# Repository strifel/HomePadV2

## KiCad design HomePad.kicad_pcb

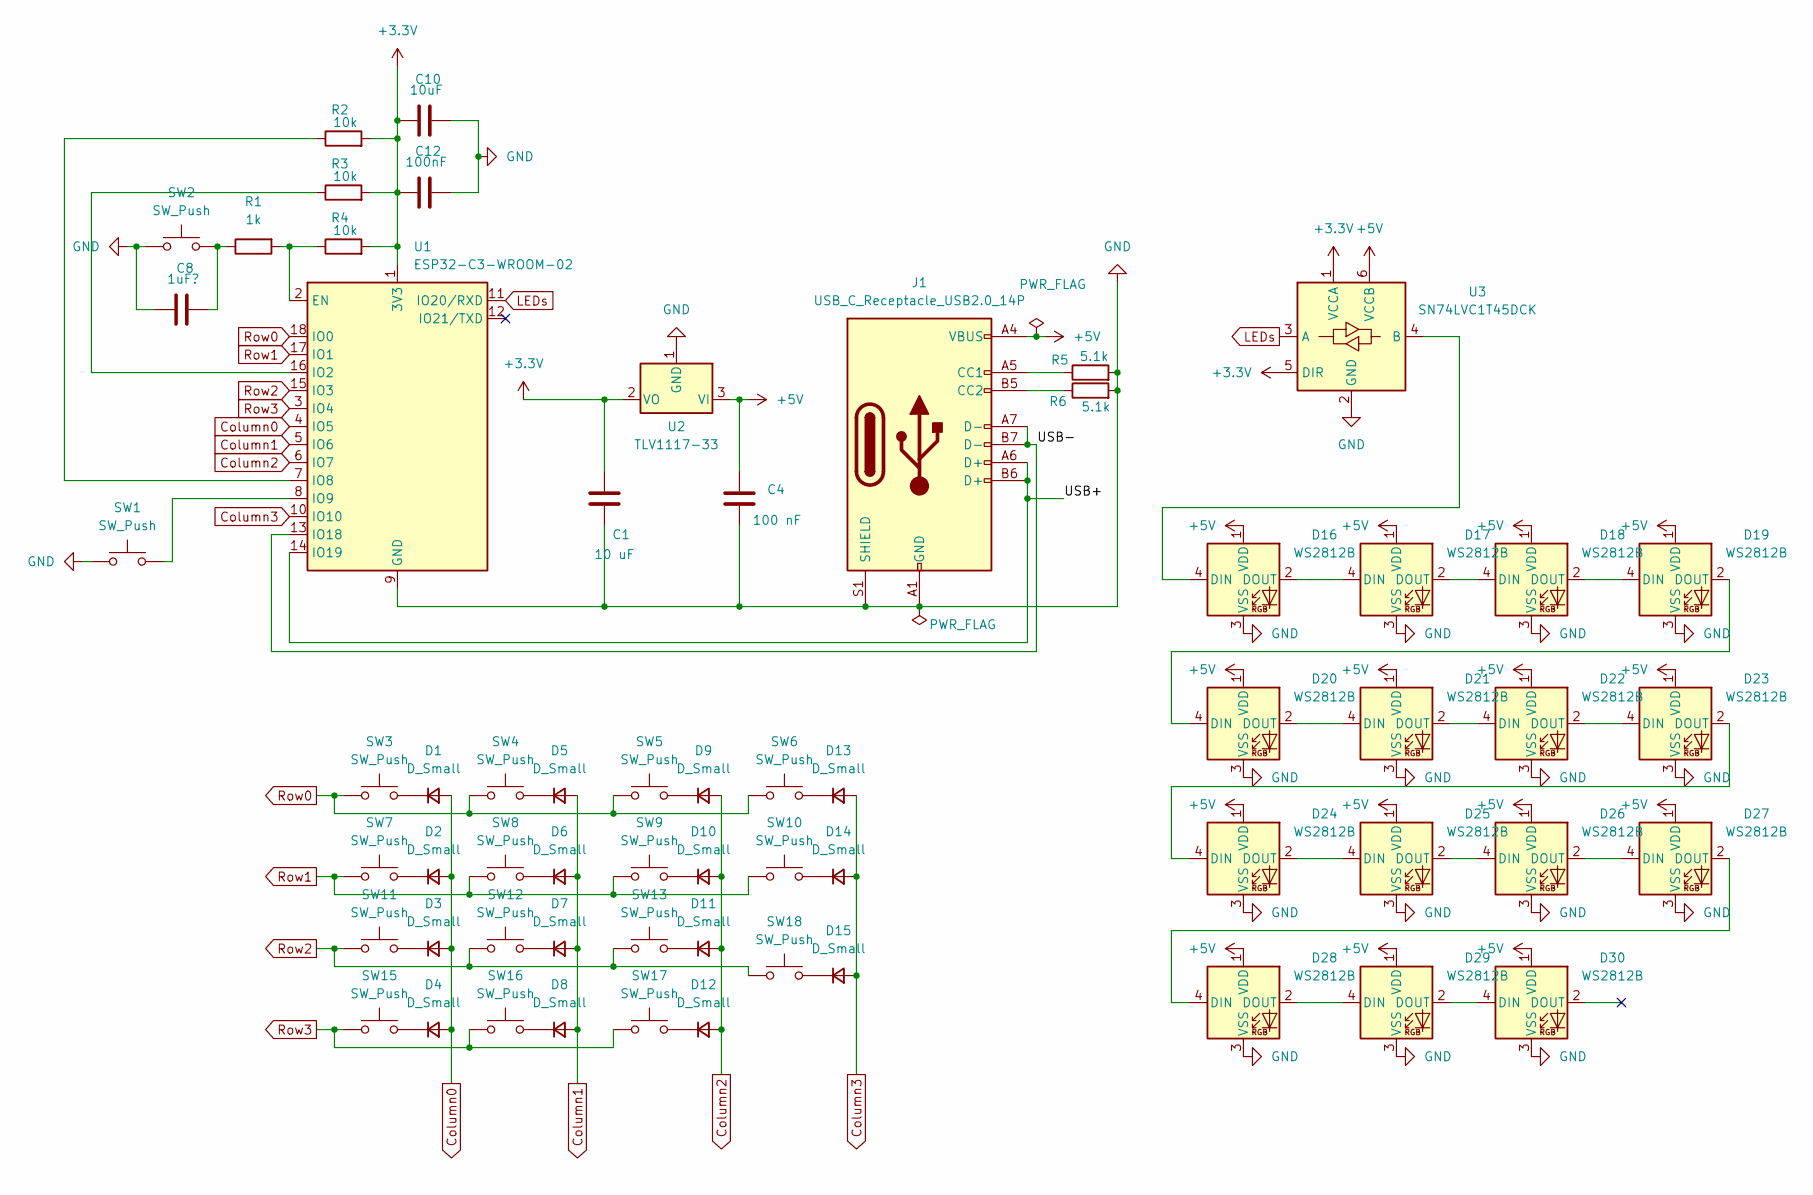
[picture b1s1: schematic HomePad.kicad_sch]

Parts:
C1: 10 uF; C_0603_1608Metric_Pad1.08x0.95mm_HandSolder; LCSC C85713
C4: 100 nF; C_0603_1608Metric_Pad1.08x0.95mm_HandSolder
C8: 1uF?; C_0603_1608Metric_Pad1.08x0.95mm_HandSolder
C10: 10uF; C_0603_1608Metric_Pad1.08x0.95mm_HandSolder
C12: 100nF; C_0603_1608Metric_Pad1.08x0.95mm_HandSolder
D1, D5: D_Small; D_0603_1608Metric_Pad1.05x0.95mm_HandSolder; LCSC C30584800
D2, D3, D4, D6, D7, D8, D9, D10, D11, D12, D13, D14, D15: D_Small; D_0603_1608Metric_Pad1.05x0.95mm_HandSolder
D16, D17, D18, D19, D20, D21, D22, D23, D24, D25, D26, D27, D28, D29, D30: WS2812B; LED-SMD_4P_XL-6028RGBW-WS2812B
J1: USB_C_Receptacle_USB2.0_14P; USB_C_Receptacle_HRO_TYPE-C-31-M-12; LCSC C2765186
R1: 1k; R_0603_1608Metric_Pad0.98x0.95mm_HandSolder; LCSC C2907113
R2, R3, R4: 10k; R_0603_1608Metric_Pad0.98x0.95mm_HandSolder; LCSC C25804
R5, R6: 5.1k; R_0603_1608Metric_Pad0.98x0.95mm_HandSolder; LCSC C23186
SW1, SW2: SW_Push; SW_Push_SPST_NO_Alps_SKRK; LCSC C2874432
SW3, SW4, SW5, SW6, SW7, SW8, SW9, SW10, SW11, SW12, SW13, SW15, SW16, SW17, SW18: SW_Push; SW_MX_HS_CPG151101S11_1u
U1: ESP32-C3-WROOM-02
U2: TLV1117-33; SOT-223-3_TabPin2; LCSC Part # C91728
U3: SN74LVC1T45DCK; SOT-363_SC-70-6_Handsoldering; LCSC C168855

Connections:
+3.3V: C1.1, C10.2, C12.2, R2.2, R3.2, R4.2, U1.1 (3V3), U2.2 (VO), U3.1 (VCCA), U3.5 (DIR)
+5V: C4.1, D16.1 (VDD), D17.1 (VDD), D18.1 (VDD), D19.1 (VDD), D20.1 (VDD), D21.1 (VDD), D22.1 (VDD), D23.1 (VDD), D24.1 (VDD), D25.1 (VDD), D26.1 (VDD), D27.1 (VDD), D28.1 (VDD), D29.1 (VDD), D30.1 (VDD), J1.A4 (VBUS), J1.A9 (VBUS), J1.B4 (VBUS), J1.B9 (VBUS), U2.3 (VI), U3.6 (VCCB)
/USB+: J1.A6 (D+), J1.B6 (D+), U1.14 (IO19)
/USB-: J1.A7 (D-), J1.B7 (D-), U1.13 (IO18)
Column0: D1.2 (A), D2.2 (A), D3.2 (A), D4.2 (A), U1.4 (IO5)
Column1: D5.2 (A), D6.2 (A), D7.2 (A), D8.2 (A), U1.5 (IO6)
Column2: D9.2 (A), D10.2 (A), D11.2 (A), D12.2 (A), U1.6 (IO7)
Column3: D13.2 (A), D14.2 (A), D15.2 (A), U1.10 (IO10)
GND: C1.2, C4.2, C8.2, C10.1, C12.1, D16.3 (VSS), D17.3 (VSS), D18.3 (VSS), D19.3 (VSS), D20.3 (VSS), D21.3 (VSS), D22.3 (VSS), D23.3 (VSS), D24.3 (VSS), D25.3 (VSS), D26.3 (VSS), D27.3 (VSS), D28.3 (VSS), D29.3 (VSS), D30.3 (VSS), J1.A1 (GND), J1.A12 (GND), J1.B1 (GND), J1.B12 (GND), J1.S1 (SHIELD), R5.2, R6.2, SW1.1, SW2.1, U1.9 (GND), U1.19 (GND), U2.1 (GND), U3.2 (GND)
LEDs: U1.11 (IO20/RXD), U3.3 (A)
unnamed: C8.1, R1.1, SW2.2
unnamed: D1.1 (K), SW3.2
unnamed: D2.1 (K), SW7.2
unnamed: D3.1 (K), SW11.2
unnamed: D4.1 (K), SW15.2
unnamed: D5.1 (K), SW4.2
unnamed: D6.1 (K), SW8.2
unnamed: D7.1 (K), SW12.2
unnamed: D8.1 (K), SW16.2
unnamed: D9.1 (K), SW5.2
unnamed: D10.1 (K), SW9.2
unnamed: D11.1 (K), SW13.2
unnamed: D12.1 (K), SW17.2
unnamed: D13.1 (K), SW6.2
unnamed: D14.1 (K), SW10.2
unnamed: D15.1 (K), SW18.2
unnamed: D16.4 (DIN), U3.4 (B)
unnamed: D16.2 (DOUT), D17.4 (DIN)
unnamed: D17.2 (DOUT), D18.4 (DIN)
unnamed: D18.2 (DOUT), D19.4 (DIN)
unnamed: D19.2 (DOUT), D20.4 (DIN)
unnamed: D20.2 (DOUT), D21.4 (DIN)
unnamed: D21.2 (DOUT), D22.4 (DIN)
unnamed: D22.2 (DOUT), D23.4 (DIN)
unnamed: D23.2 (DOUT), D24.4 (DIN)
unnamed: D24.2 (DOUT), D25.4 (DIN)
unnamed: D25.2 (DOUT), D26.4 (DIN)
unnamed: D26.2 (DOUT), D27.4 (DIN)
unnamed: D27.2 (DOUT), D28.4 (DIN)
unnamed: D28.2 (DOUT), D29.4 (DIN)
unnamed: D29.2 (DOUT), D30.4 (DIN)
unnamed: J1.A5 (CC1), R5.1
unnamed: J1.B5 (CC2), R6.1
unnamed: R1.2, R4.1, U1.2 (EN)
unnamed: R3.1, U1.16 (IO2)
unnamed: R2.1, U1.7 (IO8)
unnamed: SW1.2, U1.8 (IO9)
Row0: SW3.1, SW4.1, SW5.1, SW6.1, U1.18 (IO0)
Row1: SW7.1, SW8.1, SW9.1, SW10.1, U1.17 (IO1)
Row2: SW11.1, SW12.1, SW13.1, SW18.1, U1.15 (IO3)
Row3: SW15.1, SW16.1, SW17.1, U1.3 (IO4)

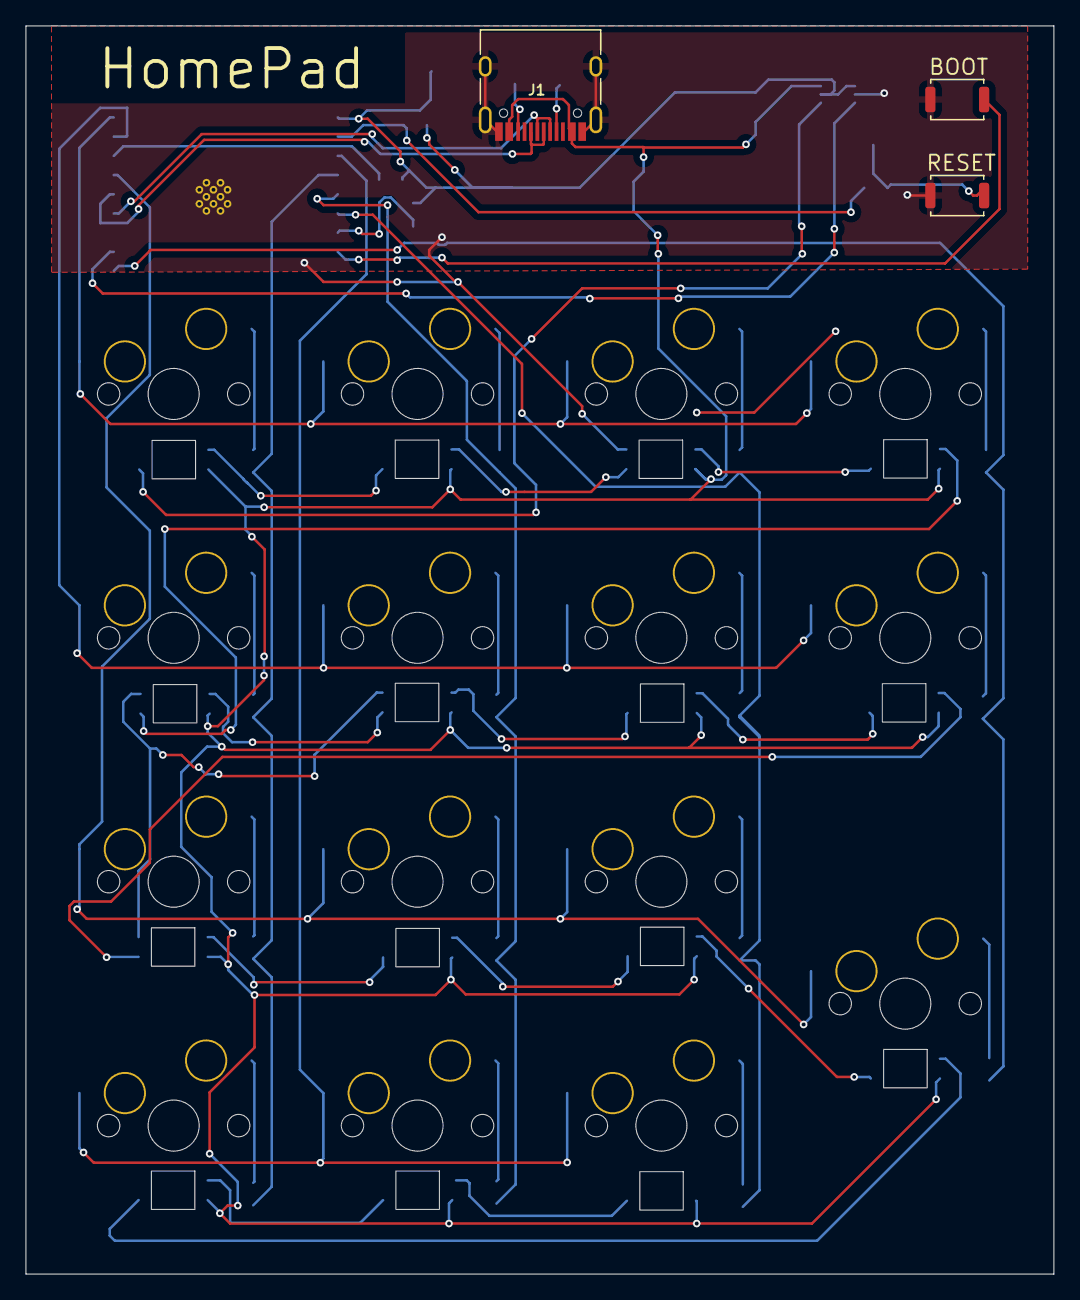
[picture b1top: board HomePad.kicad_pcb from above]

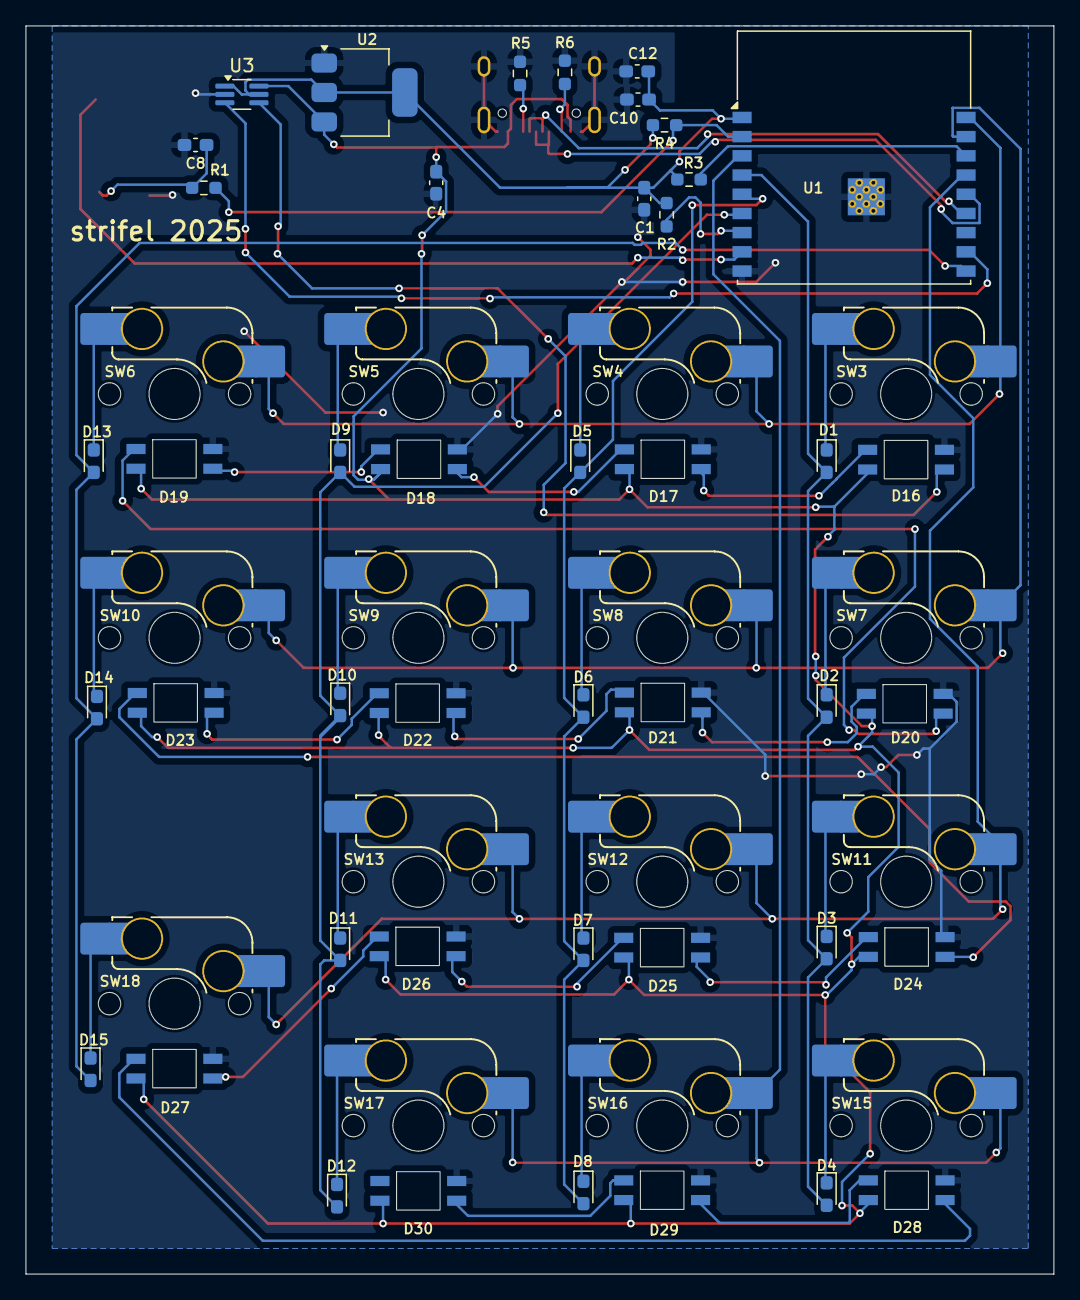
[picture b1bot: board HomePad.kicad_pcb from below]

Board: 2 copper layers, 80.3 x 97.5 mm, 62 parts (59 on the bottom side), 51 nets.

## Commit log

2025-08-20 Add firmware
2025-08-20 Create workflow
